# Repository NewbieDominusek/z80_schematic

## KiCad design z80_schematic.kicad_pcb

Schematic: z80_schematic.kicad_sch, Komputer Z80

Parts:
C1: 1000u; C_Rect_L41.5mm_W11.0mm_P37.50mm_MKS4
C2, C3, C5, C6, C7, C8, C9, C10, C11, C12, C13, C15, C17, C20, C25, C26, C27, C28, C31, C32, C34, C35, C36, C37, C38, C39: 100n; C_Disc_D6.0mm_W2.5mm_P5.00mm
C4: 10n; C_Disc_D3.8mm_W2.6mm_P2.50mm
C14: 470u; C_Radial_D10.0mm_H20.0mm_P5.00mm
C16: 47u; C_Radial_D5.0mm_H11.0mm_P2.00mm
C18, C19, C21, C23, C24: 220u; C_Radial_D6.3mm_H11.0mm_P2.50mm
C29: 150p; C_Disc_D3.8mm_W2.6mm_P2.50mm
C30: 47p; C_Disc_D6.0mm_W2.5mm_P5.00mm
C33, C40: 1u; C_Disc_D5.1mm_W3.2mm_P5.00mm
D23, D24, D25, D26, D27, D28, D29, D30, D31, D32, D33, D34, D36, D37, D38: LED; LED_D5.0mm
J1, J2, J4, J6: Conn_01x14_Socket; PinSocket_1x14_P2.54mm_Vertical
J5: EXTERNAL_CLOCK; PinSocket_1x02_P2.54mm_Vertical
J7: 5V_IN; PhoenixContact_MSTBVA_2,5_2-G_1x02_P5.00mm_Vertical
L1: 470u; L_Axial_L11.0mm_D4.5mm_P15.24mm_Horizontal_Fastron_MECC
Q1, Q3, Q4, Q41, Q42, Q43, Q44, Q90, Q98: 2N7002; SOT-23
Q13, Q14, Q16, Q45, Q46, Q47, Q49, Q50, Q51, Q52, Q53, Q54, Q55, Q56, Q57, Q58, Q59, Q60, Q61, Q62, Q63, Q64, Q65, Q66, Q67, Q68, Q69, Q70, Q71, Q72, Q73, Q74, Q75, Q76, Q77, Q78, Q79, Q80, Q81, Q82, Q83, Q84, Q85, Q86, Q87, Q88, Q89, Q91, Q92, Q93, Q94, Q95, Q96, Q97: BSS84; SOT-23
Q48: Q_NPN_EBC; TO-18-3
R1, R4, R6, R11, R13, R14, R15, R32, R49, R50, R51, R52, R53, R54, R55, R56, R57, R58, R62, R64, R65, R66, R67, R68, R69, R70, R94, R95, R96, R97, R107, R109, R112, R113, R118, R119, R120, R121, R126, R127, R128, R129, R132, R133, R135, R136, R137, R138, R139, R140, R141, R142, R151, R152, R153, R154, R155, R156, R157, R166, R167, R168, R169, R170, R171, R172: 1k; R_1206_3216Metric_Pad1.30x1.75mm_HandSolder
R2: 1M; R_Axial_DIN0204_L3.6mm_D1.6mm_P7.62mm_Horizontal
R3, R16: 10k; R_Axial_DIN0411_L9.9mm_D3.6mm_P15.24mm_Horizontal
R5: 100; R_1206_3216Metric_Pad1.30x1.75mm_HandSolder
R59: 68k; R_Axial_DIN0411_L9.9mm_D3.6mm_P15.24mm_Horizontal
R60, R63: 4k7; R_Axial_DIN0411_L9.9mm_D3.6mm_P15.24mm_Horizontal
R61: 20k; R_Axial_DIN0411_L9.9mm_D3.6mm_P15.24mm_Horizontal
SW1: RESET; SW_PUSH_6mm_H5mm
SW2: CLK_STEP; SW_PUSH_6mm_H5mm
SW3: SW_SPST; PhoenixContact_MSTBVA_2,5_2-G_1x02_P5.00mm_Vertical
SW4: ADDR_BUS_BUFFERS; SPDT_SWITCH_OS102011MS2QN1
SW5: SW_SPDT; SPDT_SWITCH_OS102011MS2QN1
SW6: CLOCK_SEL; SPDT_SWITCH_OS102011MS2QN1
SW8: CLK_SOURCE_SEL; SPDT_SWITCH_OS102011MS2QN1
U1: Z80CPU; DIP_Socket-40_W11.9mm_W12.7mm_W15.24mm_W17.78mm_W18.5mm_3M_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
U2, U31: Z84C20; DIP-40_W15.24mm_Socket_LongPads
U3: TC551001CP-70L; DIP_Socket-32_W11.9mm_W12.7mm_W15.24mm_W17.78mm_W18.5mm_3M_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
U4, U7, U16, U17: 74LS241; DIP-20_W7.62mm_Socket_LongPads
U5: W27E512; DIP_Socket-28_W11.9mm_W12.7mm_W15.24mm_W17.78mm_W18.5mm_3M_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
U6: NE555P; DIP-8_W7.62mm_Socket_LongPads
U8: 74HC374; DIP-20_W7.62mm_Socket_LongPads
U9: SN74ACT08N; DIP-14_W7.62mm_Socket_LongPads
U10: AT28C64B-15PU; DIP_Socket-28_W11.9mm_W12.7mm_W15.24mm_W17.78mm_W18.5mm_3M_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
U11: W49F002; DIP_Socket-32_W11.9mm_W12.7mm_W15.24mm_W17.78mm_W18.5mm_3M_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
U12: 74HC14; SO-14_3.9x8.65mm_P1.27mm
U15: SN74AC32; DIP-14_W7.62mm_Socket_LongPads
U20, U21, U22, U23, U28, U30: ATF16V8Bxx-xxPU; DIP-20_W7.62mm_Socket_LongPads
U24, U25, U26, U27, U29, U32: D148K; D1X8K

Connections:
1MHz_CLK: SW8.3 (C), U12.6
+5V: C1.1, C5.1, C6.1, C7.1, C8.2, C9.1, C10.1, C11.2, C12.1, C13.1, C14.1, C15.1, C16.1, C17.1, C18.1, C19.1, C20.1, C21.1, C23.1, C24.1, C25.1, C26.1, C27.1, C28.1, C34.1, C35.1, C36.1, C37.1, C38.1, C39.1, C40.2, D36.2 (A), D37.2 (A), D38.2 (A), J1.1, J1.2, J2.1, J2.2, J4.1, J4.2, J6.1, J6.2, Q13.2 (S), Q14.2 (S), Q16.2 (S), Q45.2 (S), Q46.2 (S), Q47.2 (S), Q49.2 (S), Q50.2 (S), Q51.2 (S), Q52.2 (S), Q53.2 (S), Q54.2 (S), Q55.2 (S), Q56.2 (S), Q57.2 (S), Q58.2 (S), Q59.2 (S), Q60.2 (S), Q61.2 (S), Q62.2 (S), Q63.2 (S), Q64.2 (S), Q65.2 (S), Q66.2 (S), Q67.2 (S), Q68.2 (S), Q69.2 (S), Q70.2 (S), Q71.2 (S), Q72.2 (S), Q73.2 (S), Q74.2 (S), Q75.2 (S), Q76.2 (S), Q77.2 (S), Q78.2 (S), Q79.2 (S), Q80.2 (S), Q81.2 (S), Q82.2 (S), Q83.2 (S), Q84.2 (S), Q85.2 (S), Q86.2 (S), Q87.2 (S), Q88.2 (S), Q89.2 (S), Q91.2 (S), Q92.2 (S), Q93.2 (S), Q94.2 (S), Q95.2 (S), Q96.2 (S), Q97.2 (S), R1.2, R2.1, R3.2, R4.1, R6.1, R13.2, R14.2, R15.1, R16.1, R32.1, R59.1, R60.1, SW3.2 (B), SW4.1 (A), SW5.1 (A), U1.11 (VCC), U2.26 (VCC), U3.32 (VDD), U4.20 (VCC), U5.28 (VCC), U6.4 (R), U6.8 (VCC), U7.20 (VCC), U8.20 (VCC), U9.14 (VDD), U10.28 (VCC), U11.32 (VCC), U12.14 (VCC), U15.14 (VDD), U16.20 (VCC), U17.20 (VCC), U20.1 (I), U20.6 (I5), U20.7 (I6), U20.8 (I7), U20.9 (I8), U20.20 (V_{CC}), U21.1 (I), U21.6 (I5), U21.7 (I6), U21.8 (I7), U21.9 (I8), U21.20 (V_{CC}), U22.1 (I), U22.6 (I5), U22.7 (I6), U22.8 (I7), U22.9 (I8), U22.20 (V_{CC}), U23.1 (I), U23.6 (I5), U23.7 (I6), U23.8 (I7), U23.9 (I8), U23.20 (V_{CC}), U28.1 (I), U28.6 (I5), U28.7 (I6), U28.8 (I7), U28.9 (I8), U28.20 (V_{CC}), U30.1 (I), U30.6 (I5), U30.7 (I6), U30.8 (I7), U30.9 (I8), U30.20 (V_{CC}), U31.26 (VCC)
/ADR0: U2.6 (B/~A), U3.12 (A0), U4.18 (O0a), U5.10 (A0), U10.10 (A0), U11.12 (A0), U21.2 (I1), U31.6 (B/~A)
/ADR1: U2.5 (C/~D), U3.11 (A1), U4.16 (O1a), U5.9 (A1), U10.9 (A1), U11.11 (A1), U21.3 (I2), U31.5 (C/~D)
/ADR2: U3.10 (A2), U4.14 (O2a), U5.8 (A2), U10.8 (A2), U11.10 (A2), U21.4 (I3)
/ADR3: U3.9 (A3), U4.12 (O3a), U5.7 (A3), U10.7 (A3), U11.9 (A3), U21.5 (I4)
/ADR4: U3.8 (A4), U4.9 (O0b), U5.6 (A4), U10.6 (A4), U11.8 (A4), U22.2 (I1)
/ADR5: U3.7 (A5), U4.7 (O1b), U5.5 (A5), U10.5 (A5), U11.7 (A5), U22.3 (I2)
/ADR6: U3.6 (A6), U4.5 (O2b), U5.4 (A6), U10.4 (A6), U11.6 (A6), U22.4 (I3)
/ADR7: U3.5 (A7), U4.3 (O3b), U5.3 (A7), U10.3 (A7), U11.5 (A7), U22.5 (I4)
/ADR8: U3.27 (A8), U5.25 (A8), U7.18 (O0a), U10.25 (A8), U11.27 (A8), U23.2 (I1)
/ADR9: U3.26 (A9), U5.24 (A9), U7.16 (O1a), U10.24 (A9), U11.26 (A9), U23.3 (I2)
/ADR10: U3.23 (A10), U5.21 (A10), U7.14 (O2a), U10.21 (A10), U11.23 (A10), U23.4 (I3)
/ADR11: U3.25 (A11), U5.23 (A11), U7.12 (O3a), U10.23 (A11), U11.25 (A11), U23.5 (I4)
/ADR12: U3.4 (A12), U5.2 (A12), U7.9 (O0b), U10.2 (A12), U11.4 (A12), U20.2 (I1)
/ADR13: U3.28 (A13), U5.26 (A13), U7.7 (O1b), U20.3 (I2)
/ADR14: U3.3 (A14), U5.27 (A14), U7.5 (O2b), U20.4 (I3)
/ADR15: U5.1 (A15), U7.3 (O3b), U9.1 (1A), U20.5 (I4)
/A_ARDY: J1.13, U2.18 (ARDY)
/A_BRDY: J2.13, U2.21 (BRDY)
/A_PA0: J1.5, U2.15 (PA0)
/A_PA1: J1.6, U2.14 (PA1)
/A_PA2: J1.7, U2.13 (PA2)
/A_PA3: J1.8, U2.12 (PA3)
/A_PA4: J1.9, U2.10 (PA4)
/A_PA5: J1.10, U2.9 (PA5)
/A_PA6: J1.11, U2.8 (PA6)
/A_PA7: J1.12, U2.7 (PA7)
/A_PB0: J2.5, U2.27 (PB0)
/A_PB1: J2.6, U2.28 (PB1)
/A_PB2: J2.7, U2.29 (PB2)
/A_PB3: J2.8, U2.30 (PB3)
/A_PB4: J2.9, U2.31 (PB4)
/A_PB5: J2.10, U2.32 (PB5)
/A_PB6: J2.11, U2.33 (PB6)
/A_PB7: J2.12, U2.34 (PB7)
/B_ARDY: J4.13, U31.18 (ARDY)
/B_BRDY: J6.13, U31.21 (BRDY)
/B_PA0: J4.5, U31.15 (PA0)
/B_PA1: J4.6, U31.14 (PA1)
/B_PA2: J4.7, U31.13 (PA2)
/B_PA3: J4.8, U31.12 (PA3)
/B_PA4: J4.9, U31.10 (PA4)
/B_PA5: J4.10, U31.9 (PA5)
/B_PA6: J4.11, U31.8 (PA6)
/B_PA7: J4.12, U31.7 (PA7)
/B_PB0: J6.5, U31.27 (PB0)
/B_PB1: J6.6, U31.28 (PB1)
/B_PB2: J6.7, U31.29 (PB2)
/B_PB3: J6.8, U31.30 (PB3)
/B_PB4: J6.9, U31.31 (PB4)
/B_PB5: J6.10, U31.32 (PB5)
/B_PB6: J6.11, U31.33 (PB6)
/B_PB7: J6.12, U31.34 (PB7)
/DATA0: U1.14 (D0), U2.19 (D0), U3.13 (D0), U8.3 (D0), U10.11 (I/O0), U11.13 (I/O0), U28.2 (I1), U31.19 (D0)
/DATA1: U1.15 (D1), U2.20 (D1), U3.14 (D1), U8.4 (D1), U10.12 (I/O1), U11.14 (I/O1), U28.3 (I2), U31.20 (D1)
/DATA2: U1.12 (D2), U2.1 (D2), U3.15 (D2), U8.7 (D2), U10.13 (I/O2), U11.15 (I/O2), U28.4 (I3), U31.1 (D2)
/DATA3: U1.8 (D3), U2.40 (D3), U3.17 (D3), U8.8 (D3), U10.15 (I/O3), U11.17 (I/O3), U28.5 (I4), U31.40 (D3)
/DATA4: U1.7 (D4), U2.39 (D4), U3.18 (D4), U8.13 (D4), U10.16 (I/O4), U11.18 (I/O4), U30.2 (I1), U31.39 (D4)
/DATA5: U1.9 (D5), U2.38 (D5), U3.19 (D5), U8.14 (D5), U10.17 (I/O5), U11.19 (I/O5), U30.3 (I2), U31.38 (D5)
/DATA6: U1.10 (D6), U2.3 (D6), U3.20 (D6), U8.17 (D6), U10.18 (I/O6), U11.20 (I/O6), U30.4 (I3), U31.3 (D6)
/DATA7: U1.13 (D7), U2.2 (D7), U3.21 (D7), U8.18 (D7), U10.19 (I/O7), U11.21 (I/O7), U30.5 (I4), U31.2 (D7)
/~A_ASTB: J1.14, U2.16 (~ASTB)
/~A_BSTB: J2.14, U2.17 (~BSTB)
/~B_ASTB: J4.14, U31.16 (~ASTB)
/~B_BSTB: J6.14, U31.17 (~BSTB)
BIOS_LATCH: U5.18 (I/O6), U9.5 (2B), U17.6 (I2a)
BIOS_PAGE_SEL_0: U8.2 (O0), U11.28 (A13)
BIOS_PAGE_SEL_1: U8.5 (O1), U11.29 (A14)
BIOS_PAGE_SEL_2: U8.6 (O2), U11.3 (A15)
BIOS_PAGE_SEL_3: U8.9 (O3), U11.2 (A16)
BIOS_PAGE_SEL_4: U8.12 (O4), U11.30 (A17)
CLK: SW6.2 (B), U1.6 (~CLK), U2.25 (CLK), U17.8 (I3a), U31.25 (CLK)
CLK_SINGLE: SW6.3 (C), U6.3 (Q)
GND: C1.2, C2.2, C3.2, C4.1, C5.2, C6.2, C7.2, C8.1, C9.2, C10.2, C11.1, C12.2, C13.2, C14.2, C15.2, C16.2, C17.2, C18.2, C19.2, C20.2, C21.2, C23.2, C24.2, C25.2, C26.2, C27.2, C28.2, C29.2, C30.2, C33.1, C34.2, C35.2, C36.2, C37.2, C38.2, C39.2, C40.1, J1.3, J1.4, J2.3, J2.4, J4.3, J4.4, J5.1, J6.3, J6.4, J7.1, Q1.2 (S), Q3.2 (S), Q4.2 (S), Q41.2 (S), Q42.2 (S), Q43.2 (S), Q44.2 (S), Q90.2 (S), Q98.2 (S), R5.1, R11.1, R62.2, R63.2, R107.1, R109.1, R112.1, R113.1, R118.1, R119.1, R120.1, R121.1, R126.1, R127.1, R128.1, R129.1, SW2.1, SW4.3 (C), SW5.3 (C), U1.29 (GND), U2.11 (GND), U3.16 (GND), U4.10 (GND), U5.14 (GND), U5.20 (~CE), U5.22 (~OE), U6.1 (GND), U7.10 (GND), U8.10 (GND), U9.7 (GND), U9.9 (3A), U9.10 (3B), U9.12 (4A), U9.13 (4B), U10.14 (GND), U11.16 (GND), U12.7 (GND), U12.11, U15.7 (GND), U16.10 (GND), U17.2 (I0a), U17.10 (GND), U20.10 (GND), U21.10 (GND), U22.10 (GND), U23.10 (GND), U28.10 (GND), U30.10 (GND), U31.11 (GND)
MONITOR_EN: U12.2, U16.19 (OEb), U17.19 (OEb), U20.11 (I9), U21.11 (I9), U22.11 (I9), U23.11 (I9), U28.11 (I9), U30.11 (I9)
unnamed: C29.1, C31.2, L1.1
unnamed: C30.1, C32.2, L1.2
unnamed: D23.2 (A), Q13.3 (D)
unnamed: D23.1 (K), R107.2
unnamed: D24.2 (A), Q14.3 (D)
unnamed: D24.1 (K), R109.2
unnamed: D25.2 (A), Q16.3 (D)
unnamed: D25.1 (K), R112.2
unnamed: D26.2 (A), Q49.3 (D)
unnamed: D26.1 (K), R113.2
unnamed: D27.2 (A), Q50.3 (D)
unnamed: D27.1 (K), R118.2
unnamed: D28.2 (A), Q51.3 (D)
unnamed: D28.1 (K), R119.2
unnamed: D29.2 (A), Q52.3 (D)
unnamed: D29.1 (K), R120.2
unnamed: D30.2 (A), Q53.3 (D)
unnamed: D30.1 (K), R121.2
unnamed: D31.2 (A), Q54.3 (D)
unnamed: D31.1 (K), R126.2
unnamed: D32.2 (A), Q55.3 (D)
unnamed: D32.1 (K), R127.2
unnamed: D33.2 (A), Q56.3 (D)
unnamed: D33.1 (K), R128.2
unnamed: D34.2 (A), Q57.3 (D)
unnamed: D34.1 (K), R129.2
unnamed: D36.1 (K), R132.2
unnamed: D37.1 (K), R133.2
unnamed: D38.1 (K), R135.2
unnamed: J5.2, SW8.1 (A)
unnamed: J7.2, SW3.1 (A)
unnamed: Q1.3 (D), R132.1
unnamed: Q1.1 (G), U17.12 (O3a)
unnamed: Q3.3 (D), R133.1
unnamed: Q3.1 (G), U17.14 (O2a)
unnamed: Q4.3 (D), R135.1
unnamed: Q4.1 (G), U17.16 (O1a)
unnamed: Q13.1 (G), U16.18 (O0a)
unnamed: Q14.1 (G), U16.16 (O1a)
unnamed: Q16.1 (G), U16.14 (O2a)
unnamed: Q41.3 (D), U24.3 (CC), U24.8 (CC)
unnamed: Q41.1 (G), U20.19 (I/O)
unnamed: Q42.3 (D), U25.3 (CC), U25.8 (CC)
unnamed: Q42.1 (G), U21.19 (I/O)
unnamed: Q43.3 (D), U26.3 (CC), U26.8 (CC)
unnamed: Q43.1 (G), U22.19 (I/O)
unnamed: Q44.3 (D), U27.3 (CC), U27.8 (CC)
unnamed: Q44.1 (G), U23.19 (I/O)
unnamed: Q45.3 (D), R49.1
unnamed: Q45.1 (G), U20.12 (I/O)
unnamed: Q46.3 (D), R50.1
unnamed: Q46.1 (G), U20.13 (I/O)
unnamed: Q47.3 (D), R51.1
unnamed: Q47.1 (G), U20.14 (I/O)
unnamed: C32.1, Q48.2 (B), R59.2, R61.1
unnamed: C31.1, Q48.3 (C), R60.2, U12.5
unnamed: C33.2, Q48.1 (E), R62.1
unnamed: Q49.1 (G), U16.12 (O3a)
unnamed: Q50.1 (G), U16.9 (O0b)
unnamed: Q51.1 (G), U16.7 (O1b)
unnamed: Q52.1 (G), U16.5 (O2b)
unnamed: Q53.1 (G), U16.3 (O3b)
unnamed: Q54.1 (G), U17.9 (O0b)
unnamed: Q55.1 (G), U17.7 (O1b)
unnamed: Q56.1 (G), U17.5 (O2b)
unnamed: Q57.1 (G), U17.3 (O3b)
unnamed: Q58.3 (D), R52.1
unnamed: Q58.1 (G), U20.15 (I/O)
unnamed: Q59.3 (D), R53.1
unnamed: Q59.1 (G), U20.16 (I/O)
unnamed: Q60.3 (D), R54.1
unnamed: Q60.1 (G), U20.17 (I/O)
unnamed: Q61.3 (D), R56.1
unnamed: Q61.1 (G), U20.18 (I/O)
unnamed: Q62.3 (D), R55.1
unnamed: Q62.1 (G), U21.12 (I/O)
unnamed: Q63.3 (D), R57.1
unnamed: Q63.1 (G), U21.13 (I/O)
unnamed: Q64.3 (D), R58.1
unnamed: Q64.1 (G), U21.14 (I/O)
unnamed: Q65.3 (D), R64.1
unnamed: Q65.1 (G), U21.15 (I/O)
unnamed: Q66.3 (D), R65.1
unnamed: Q66.1 (G), U21.16 (I/O)
unnamed: Q67.3 (D), R66.1
unnamed: Q67.1 (G), U21.17 (I/O)
unnamed: Q68.3 (D), R67.1
unnamed: Q68.1 (G), U21.18 (I/O)
unnamed: Q69.3 (D), R68.1
unnamed: Q69.1 (G), U22.12 (I/O)
unnamed: Q70.3 (D), R69.1
unnamed: Q70.1 (G), U22.13 (I/O)
unnamed: Q71.3 (D), R70.1
unnamed: Q71.1 (G), U22.14 (I/O)
unnamed: Q72.3 (D), R94.1
unnamed: Q72.1 (G), U22.15 (I/O)
unnamed: Q73.3 (D), R95.1
unnamed: Q73.1 (G), U22.16 (I/O)
unnamed: Q74.3 (D), R96.1
unnamed: Q74.1 (G), U22.17 (I/O)
unnamed: Q75.3 (D), R97.1
unnamed: Q75.1 (G), U22.18 (I/O)
unnamed: Q76.3 (D), R136.1
unnamed: Q76.1 (G), U23.12 (I/O)
unnamed: Q77.3 (D), R137.1
unnamed: Q77.1 (G), U23.13 (I/O)
unnamed: Q78.3 (D), R138.1
unnamed: Q78.1 (G), U23.14 (I/O)
unnamed: Q79.3 (D), R139.1
unnamed: Q79.1 (G), U23.15 (I/O)
unnamed: Q80.3 (D), R140.1
unnamed: Q80.1 (G), U23.16 (I/O)
unnamed: Q81.3 (D), R141.1
unnamed: Q81.1 (G), U23.17 (I/O)
unnamed: Q82.3 (D), R142.1
unnamed: Q82.1 (G), U23.18 (I/O)
unnamed: Q83.3 (D), R151.1
unnamed: Q83.1 (G), U28.12 (I/O)
unnamed: Q84.3 (D), R152.1
unnamed: Q84.1 (G), U28.13 (I/O)
unnamed: Q85.3 (D), R153.1
unnamed: Q85.1 (G), U28.14 (I/O)
unnamed: Q86.3 (D), R154.1
unnamed: Q86.1 (G), U28.15 (I/O)
unnamed: Q87.3 (D), R155.1
unnamed: Q87.1 (G), U28.16 (I/O)
unnamed: Q88.3 (D), R156.1
unnamed: Q88.1 (G), U28.17 (I/O)
unnamed: Q89.3 (D), R157.1
unnamed: Q89.1 (G), U28.18 (I/O)
unnamed: Q90.3 (D), U29.3 (CC), U29.8 (CC)
unnamed: Q90.1 (G), U28.19 (I/O)
unnamed: Q91.3 (D), R166.1
unnamed: Q91.1 (G), U30.12 (I/O)
unnamed: Q92.3 (D), R167.1
unnamed: Q92.1 (G), U30.13 (I/O)
unnamed: Q93.3 (D), R168.1
unnamed: Q93.1 (G), U30.14 (I/O)
unnamed: Q94.3 (D), R169.1
unnamed: Q94.1 (G), U30.15 (I/O)
unnamed: Q95.3 (D), R170.1
unnamed: Q95.1 (G), U30.16 (I/O)
unnamed: Q96.3 (D), R171.1
unnamed: Q96.1 (G), U30.17 (I/O)
unnamed: Q97.3 (D), R172.1
unnamed: Q97.1 (G), U30.18 (I/O)
unnamed: Q98.3 (D), U32.3 (CC), U32.8 (CC)
unnamed: Q98.1 (G), U30.19 (I/O)
unnamed: R5.2, SW1.1
unnamed: R61.2, R63.1
unnamed: SW4.2 (B), U4.19 (OEb), U7.19 (OEb), U12.9
unnamed: SW6.1 (A), SW8.2 (B)
unnamed: U1.30 (A0), U4.2 (I0a)
unnamed: U1.31 (A1), U4.4 (I1a)
unnamed: U1.32 (A2), U4.17 (I3b)
unnamed: U1.33 (A3), U4.6 (I2a)
unnamed: U1.34 (A4), U4.15 (I2b)
unnamed: U1.35 (A5), U4.8 (I3a)
unnamed: U1.36 (A6), U4.13 (I1b)
unnamed: U1.37 (A7), U4.11 (I0b)
unnamed: U1.38 (A8), U7.4 (I1a)
unnamed: U1.39 (A9), U7.6 (I2a)
unnamed: U1.40 (A10), U7.8 (I3a)
unnamed: U1.1 (A11), U7.2 (I0a)
unnamed: U1.2 (A12), U7.11 (I0b)
unnamed: U1.3 (A13), U7.13 (I1b)
unnamed: U1.4 (A14), U7.15 (I2b)
unnamed: U1.5 (A15), U7.17 (I3b)
unnamed: R6.2, U1.17 (~NMI), U1.24 (~WAIT), U1.25 (~BUSRQ)
unnamed: U2.24 (IEI), U31.22 (IEO)
unnamed: R1.1, U3.30 (CE2)
unnamed: U4.1 (OEa), U7.1 (OEa), U12.8
unnamed: C4.2, U6.5 (CV)
unnamed: C2.1, R2.2, U6.6 (THR), U6.7 (DIS)
unnamed: R4.2, SW2.2, U6.2 (TR)
unnamed: U8.11 (Cp), U9.6 (2Y)
unnamed: R11.2, U8.1 (OE)
unnamed: U9.2 (1B), U12.4
unnamed: U9.4 (2A), U12.12
unnamed: R13.1, U10.27 (~WE)
unnamed: R15.2, U11.1 (~RESET)
unnamed: R14.1, U11.31 (~WE)
unnamed: U3.2 (A16), U15.3 (1Y)
unnamed: U3.31 (A15), U15.6 (2Y)
unnamed: R49.2, U24.7 (A)
unnamed: R50.2, U24.6 (B)
unnamed: R51.2, U24.4 (C)
unnamed: R52.2, U24.2 (D)
unnamed: R53.2, U24.1 (E)
unnamed: R54.2, U24.9 (F)
unnamed: R56.2, U24.10 (G)
unnamed: R55.2, U25.7 (A)
unnamed: R57.2, U25.6 (B)
unnamed: R58.2, U25.4 (C)
unnamed: R64.2, U25.2 (D)
unnamed: R65.2, U25.1 (E)
unnamed: R66.2, U25.9 (F)
unnamed: R67.2, U25.10 (G)
unnamed: R68.2, U26.7 (A)
unnamed: R69.2, U26.6 (B)
unnamed: R70.2, U26.4 (C)
unnamed: R94.2, U26.2 (D)
unnamed: R95.2, U26.1 (E)
unnamed: R96.2, U26.9 (F)
unnamed: R97.2, U26.10 (G)
unnamed: R136.2, U27.7 (A)
unnamed: R137.2, U27.6 (B)
unnamed: R138.2, U27.4 (C)
unnamed: R139.2, U27.2 (D)
unnamed: R140.2, U27.1 (E)
unnamed: R141.2, U27.9 (F)
unnamed: R142.2, U27.10 (G)
unnamed: R151.2, U29.7 (A)
unnamed: R152.2, U29.6 (B)
unnamed: R153.2, U29.4 (C)
unnamed: R154.2, U29.2 (D)
unnamed: R155.2, U29.1 (E)
unnamed: R156.2, U29.9 (F)
unnamed: R157.2, U29.10 (G)
unnamed: R32.2, U31.24 (IEI)
unnamed: R166.2, U32.7 (A)
unnamed: R167.2, U32.6 (B)
unnamed: R168.2, U32.4 (C)
unnamed: R169.2, U32.2 (D)
unnamed: R170.2, U32.1 (E)
unnamed: R171.2, U32.9 (F)
unnamed: R172.2, U32.10 (G)
RAM_PAGE_SEL_0: U8.15 (O5), U15.4 (2A)
RAM_PAGE_SEL_1: U8.16 (O6), U15.1 (1A)
RAM_PAGE_SEL_OVERRIDE: U9.3 (1Y), U15.2 (1B), U15.5 (2B), U17.4 (I1a)
~BIOS_CE: U5.12 (I/O1), U11.22 (~CE), U17.15 (I2b)
~BIOS_MAIN_CE: U5.11 (I/O0), U10.20 (~CE), U17.13 (I1b)
~INT: R16.2, U1.16 (~INT), U2.23 (~INT), U16.11 (I0b), U31.23 (~INT)
~IORQ: U1.20 (~IORQ), U2.36 (~IORQ), U16.8 (I3a), U31.36 (~IORQ)
~I/O_CE_1: U2.4 (~CE), U5.15 (I/O3), U16.15 (I2b)
~I/O_CE_2: U5.16 (I/O4), U16.17 (I3b), U31.4 (~CE)
~M1: U1.27 (~M1), U2.37 (~M1), U16.13 (I1b), U31.37 (~M1)
~MONITOR_EN: SW5.2 (B), U12.1, U16.1 (OEa), U17.1 (OEa)
~MREAD: U3.24 (~OE), U10.22 (~OE), U11.24 (~OE), U15.8 (3Y)
~MREQ: U1.19 (~MREQ), U15.10 (3B), U15.12 (4A), U16.6 (I2a)
~MWRITE: U3.29 (R/~W), U12.13, U15.11 (4Y)
~RAM_CE: U3.22 (~CE1), U5.13 (I/O2), U12.3, U17.17 (I3b)
~READ: U1.21 (~RD), U2.35 (~RD), U15.9 (3A), U16.2 (I0a), U31.35 (~RD)
~RESET_SIGNAL: C3.1, R3.1, SW1.2, U1.26 (~RESET), U17.11 (I0b)
~WRITE: U1.22 (~WR), U15.13 (4B), U16.4 (I1a)

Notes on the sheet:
ADDRESS SPACE (64kB, divided into 4 main 16kB segments) 0000 - 3FFF EEPROM BIOS 0000 - 1FFF BIOS MAIN 2000 - 3FFF BIOS PAGED (32 pages, 256kB total memory) 4000 - BFFF RAM (4 pages, 128kB total memory) C000 - FFFF Misc (I/O, page switching) + LAST 8kB OF RAM (ALWAYS AVAILABLE) I/O chip 1: C000 Port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
I/O chip 2
Clock sources Single pulses 1MHz / EXTERNAL
PAGED BIOS
BIOS
DATA 0 - 3 hex decoding
RAM
Address decoding
SCHMITT power supply
ADDRESS 12 - 15 hex decoding
MAIN BIOS
Debounced CLK step button
I/O chip 1
Signal line indicators
ADDRESS 0 - 3 hex decoding
DATA 3 - 7 hex decoding
ADDRESS 4 - 7 hex decoding
TC551001CP - 128kB RAM W49F002 - 256kB PAGED BIOS AT28C64 - 16kB MAIN BIOS W27E512 - 64kB CHIP SELECT
Interrupt line pullup
Debounced reset button
ADDRESS 8 - 11 hex decoding
CPU BLOCK
template

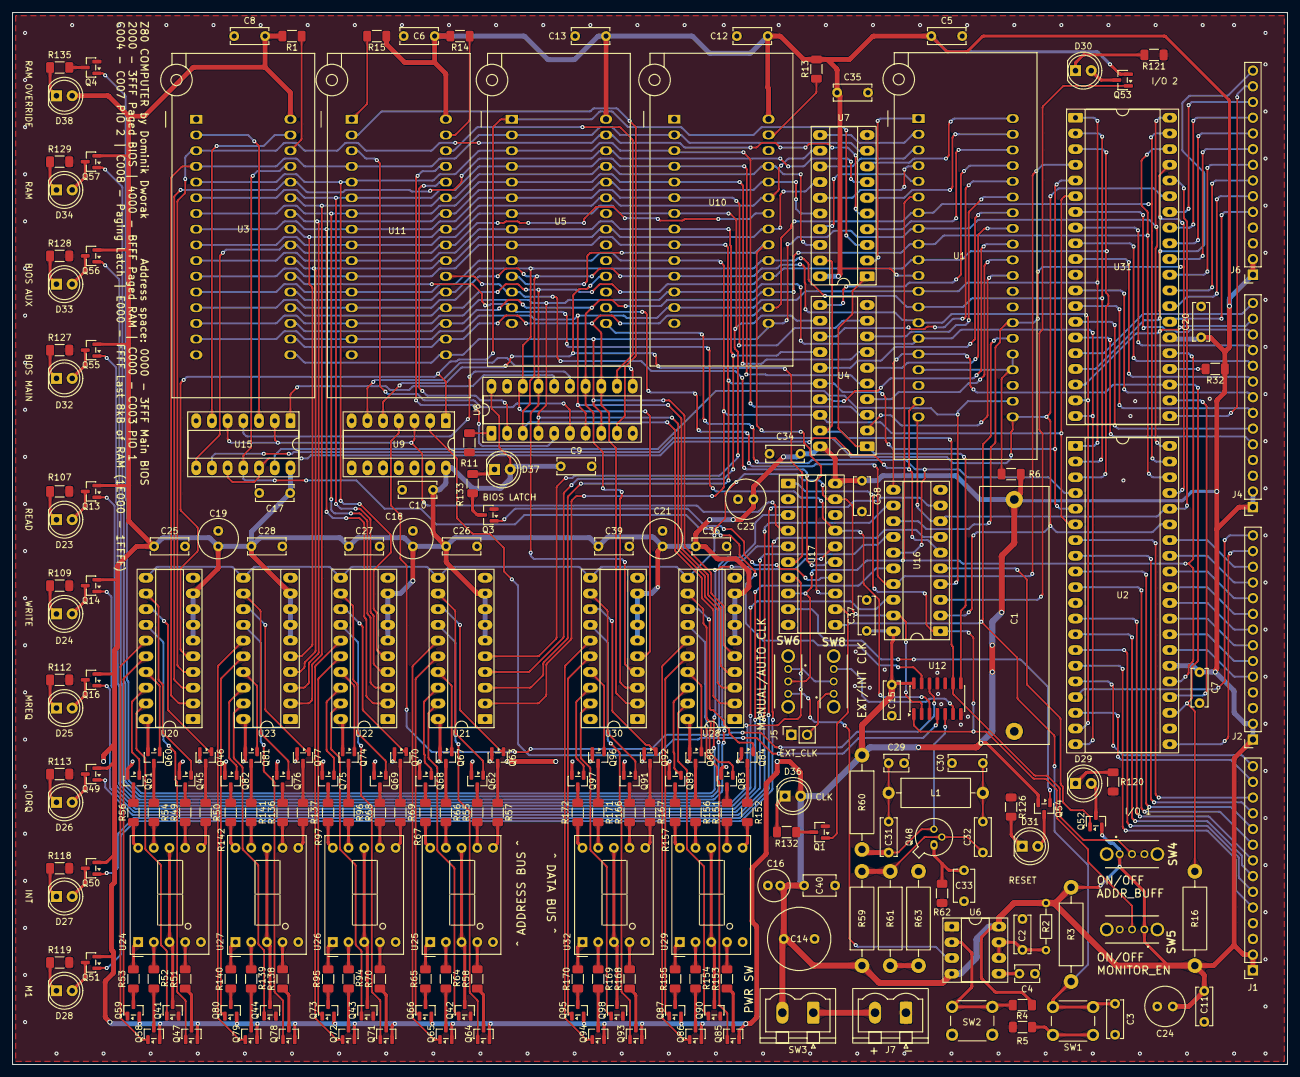
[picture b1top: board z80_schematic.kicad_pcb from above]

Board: 4 copper layers, 206.2 x 170.2 mm, 234 parts (0 on the bottom side), 321 nets.

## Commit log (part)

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2025-03-06 ROM divide
2025-08-15 asdasd
2025-10-19 Version 2.0
2025-10-20 updatus
2025-10-21 sdfsdf
2025-10-26 adasd
2025-10-27 asdas
2025-10-31 started decoding and keyboard
2025-11-10 asdsa
2025-12-19 updat
